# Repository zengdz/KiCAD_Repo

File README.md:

# KiCAD_Repo

projects move from breadboard to standard pcb

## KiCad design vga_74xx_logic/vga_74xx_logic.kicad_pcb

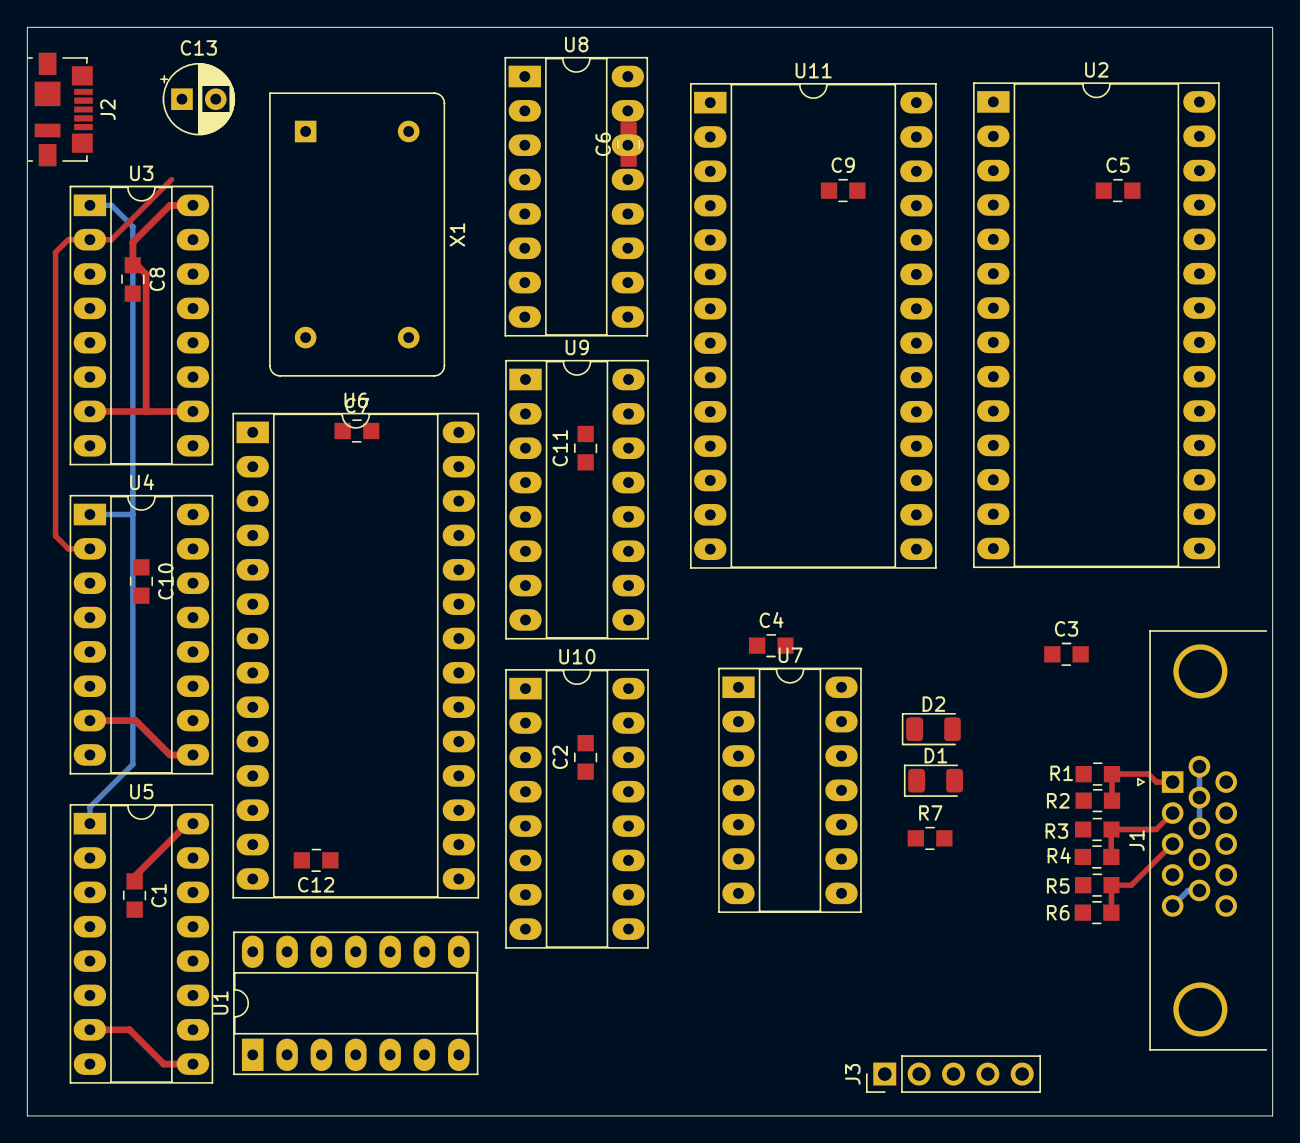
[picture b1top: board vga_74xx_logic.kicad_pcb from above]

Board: 2 copper layers, 92.1 x 80.5 mm, 37 parts (0 on the bottom side), 52 nets.

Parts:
C1, C2, C3, C4, C5, C6, C7, C8, C9, C10, C11, C12: 0.01uF; 0805
C13: 100uF; CP_Radial_D5.0mm_P2.50mm
D1, D2: 1N4148; D_1206_3216Metric
J1: DB15_Female_HighDensity; DSUB-15-HD_Female_Horizontal_P2.29x1.98mm_EdgePinOffset3.03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
J2: USB_B_Micro; USB_Micro-B_Molex_47346-0001
J3: Conn_01x05; PinHeader_1x05_P2.54mm_Vertical
R1, R3, R5: 680Ω; 0805
R2, R4, R6: 1.5K; 0805
R7: 4.7k; 0805
U1: 74LS00; DIP-14_W7.62mm_Socket_LongPads
U2, U6, U11: 28C256; DIP-28_W15.24mm_Socket_LongPads
U3, U4, U5, U8, U9, U10: 74LS161; DIP-16_W7.62mm_Socket_LongPads
U7: SN74LS00N; DIP-14_W7.62mm_Socket_LongPads
X1: 10MHz; Oscillator_DIP-14

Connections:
+5V: C1.1, C2.1, C3.1, C4.1, C5.1, C6.1, C7.1, C8.1, C9.1, C10.1, C11.1, C12.1, C13.1, J2.1, R7.1, U2.27, U2.28, U3.7, U3.9, U3.10, U3.16, U4.7, U4.9, U4.16, U5.7, U5.9, U5.16, U6.27, U6.28, U7.14, U8.7, U8.9, U8.10, U8.16, U9.7, U9.9, U9.16, U10.7, U10.9, U10.16, U11.27, U11.28, X1.14
/BLUE: J1.3, J3.3, R5.2, R6.2
/GREEN: J1.2, J3.2, R3.2, R4.2
/HSYNC: J1.13, J3.4, U1.2, U1.6
/RED: J1.1, J3.1, R1.2, R2.2
/Sheet5E2F2D48/CLK: U1.9, U3.1, U4.1, U5.1, U6.15, U8.2, U9.2, U10.2
/Sheet5E2F2D48/V_Q0: U8.14, U11.10
/Sheet5E2F2D48/V_Q1: U8.13, U11.9
/Sheet5E2F2D48/V_Q2: U8.12, U11.8
/Sheet5E2F2D48/V_Q3: U2.3, U8.11, U11.7
/Sheet5E2F2D48/V_Q4: U2.25, U9.14, U11.6
/Sheet5E2F2D48/V_Q5: U2.24, U9.13, U11.5
/Sheet5E2F2D48/V_Q6: U2.21, U9.12, U11.4
/Sheet5E2F2D48/V_Q7: U2.23, U9.11, U11.3
/Sheet5E2F2D48/V_Q8: U2.2, U10.14, U11.25
/Sheet5E2F2D48/V_Q9: U2.26, U10.13, U11.24
/Sheet5E2F2D48/count600: U7.13, U11.16
/Sheet5E2F2D48/count601: U7.1, U11.17
/Sheet5E2F2D48/count605: U7.5, U11.18
/Sheet5E2F2D48/count628: U7.9, U8.1, U9.1, U10.1, U11.19
/Sheet5E2F2D48/~VBLANK: D2.1, U7.8, U7.12
/Sheet5E28AA49/CLK: U3.2, U4.2, U5.2, X1.8
/Sheet5E28AA49/H_Q0: U3.14, U6.10
/Sheet5E28AA49/H_Q1: U2.10, U3.13, U6.9
/Sheet5E28AA49/H_Q2: U2.9, U3.12, U6.8
/Sheet5E28AA49/H_Q3: U2.8, U3.11, U6.7
/Sheet5E28AA49/H_Q4: U2.7, U4.14, U6.6
/Sheet5E28AA49/H_Q5: U2.6, U4.13, U6.5
/Sheet5E28AA49/H_Q6: U2.5, U4.12, U6.4
/Sheet5E28AA49/H_Q7: U2.4, U4.11, U6.3
/Sheet5E28AA49/H_Q8: U5.14, U6.25
/Sheet5E28AA49/count200: U1.13, U6.11
/Sheet5E28AA49/count210: U1.1, U6.12
/Sheet5E28AA49/count242: U1.5, U6.13
/Sheet5E28AA49/~HBLANK: D1.1, U1.8, U1.12
/VSYNC: J1.14, J3.5, U7.2, U7.6
GND: C1.2, C2.2, C3.2, C4.2, C5.2, C6.2, C7.2, C8.2, C9.2, C10.2, C11.2, C12.2, C13.2, J1.5, J1.6, J1.7, J1.8, J1.10, J2.5, J2.6, U2.1, U2.14, U2.20, U3.8, U4.8, U5.8, U6.1, U6.2, U6.14, U6.20, U6.21, U6.22, U6.23, U6.24, U6.26, U7.7, U8.8, U9.8, U10.8, U11.1, U11.2, U11.14, U11.20, U11.21, U11.22, U11.23, U11.26, X1.7
unnamed: D1.2, D2.2, R7.2, U2.22
unnamed: R1.1, U2.17
unnamed: R2.1, U2.16
unnamed: R3.1, U2.15
unnamed: R4.1, U2.13
unnamed: R5.1, U2.12
unnamed: R6.1, U2.11
unnamed: U1.3, U1.4
unnamed: U1.10, U1.11
unnamed: U3.15, U4.10
unnamed: U4.15, U5.10
unnamed: U7.3, U7.4
unnamed: U7.10, U7.11
unnamed: U8.15, U9.10
unnamed: U9.15, U10.10

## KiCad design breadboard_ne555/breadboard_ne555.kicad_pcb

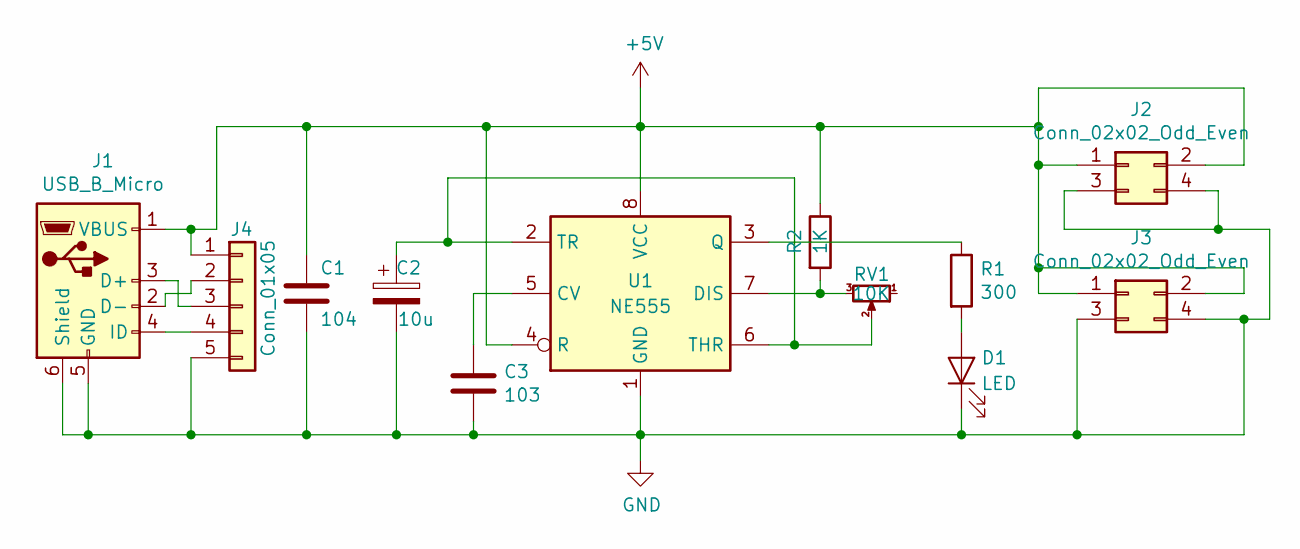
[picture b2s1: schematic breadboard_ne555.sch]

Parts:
C1: 104; 0805
C2: 10u; CP_Radial_D4.0mm_P1.50mm
C3: 103; 0805
D1: LED; 0805
J1: USB_B_Micro; USB_Micro-B_Amphenol_10104110_Horizontal
J2, J3: Conn_02x02_Odd_Even; PinHeader_2x02_P2.54mm_Vertical
J4: Conn_01x05; Wuerth_WR-WTB_64800511622_1x05_P1.50mm_Vertical
R1: 300; 0805
R2: 1K; 0805
RV1: 10K; Potentiometer_Vishay_T73YP_Vertical
U1: NE555; SO-8_3.9x4.9mm_P1.27mm

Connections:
+5V: C1.1, J1.1 (VBUS), J2.1, J2.2, J3.1, J3.2, J4.1, R2.1, U1.4 (R), U1.8 (VCC)
GND: C1.2, C2.2, C3.2, D1.1 (K), J1.5 (GND), J1.6 (Shield), J2.3, J2.4, J3.3, J3.4, J4.5, U1.1 (GND)
unnamed: C2.1, RV1.2, U1.2 (TR), U1.6 (THR)
unnamed: C3.1, U1.5 (CV)
unnamed: D1.2 (A), R1.2
unnamed: J1.2 (D-), J4.2
unnamed: J1.3 (D+), J4.3
unnamed: J1.4 (ID), J4.4
unnamed: R1.1, U1.3 (Q)
unnamed: R2.2, RV1.3, U1.7 (DIS)

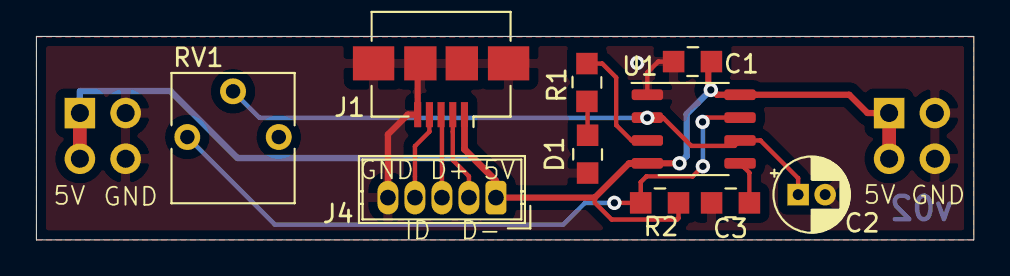
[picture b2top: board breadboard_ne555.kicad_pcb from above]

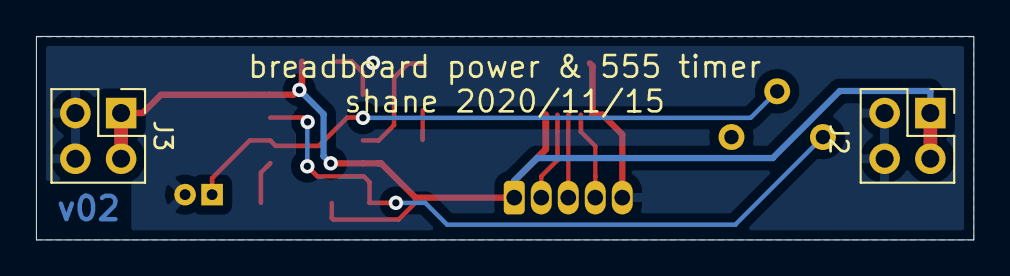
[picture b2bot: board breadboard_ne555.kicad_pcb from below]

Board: 2 copper layers, 52.1 x 11.3 mm, 12 parts (2 on the bottom side), 10 nets.

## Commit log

2020-11-12 add: breadboard_ne555 first commit
2020-11-12 fix: schematic error
2020-11-12 update: change package 0603 to 0805
2020-11-16 update change to pcb
2020-11-16 add ignore
2020-11-22 vga 74xx logic
